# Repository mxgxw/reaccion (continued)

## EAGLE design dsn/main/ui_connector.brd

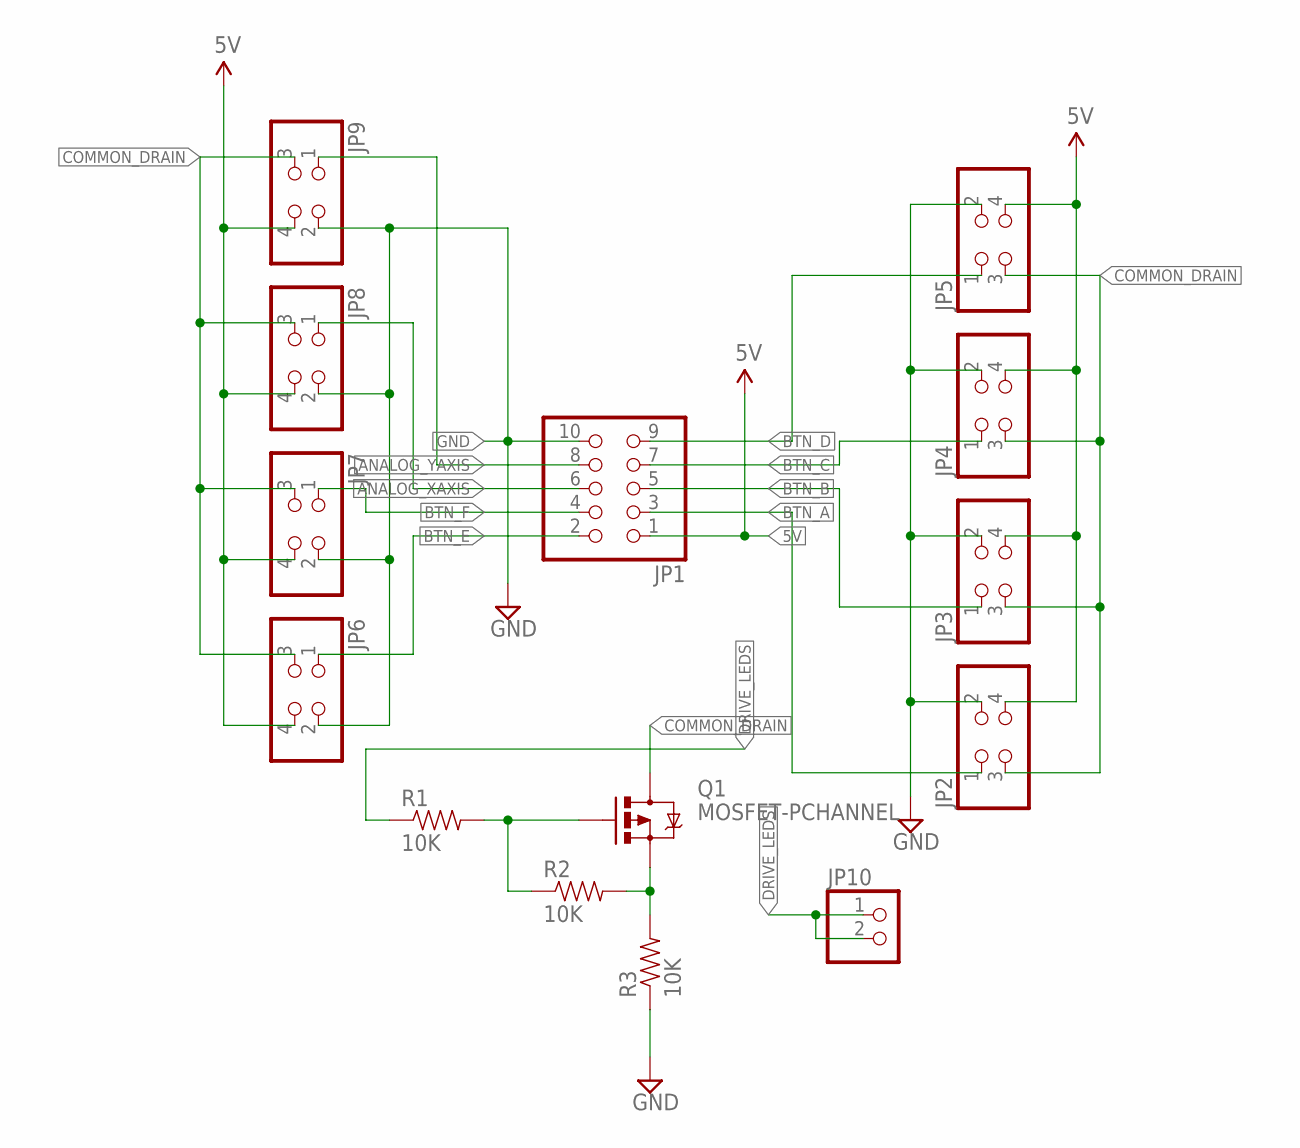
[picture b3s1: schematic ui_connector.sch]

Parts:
JP1: PINHD-2X5; 2X05
JP2, JP3, JP4, JP5, JP6, JP7, JP8, JP9: PINHD-2X2; 2X02
JP10: PINHD-1X2; 1X02
Q1: MOSFET-PCHANNEL; SOT23-3
R1, R2, R3: 10K; 0805

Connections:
5V: JP1.1, JP2.4, JP3.4, JP4.4, JP5.4, JP6.4, JP7.4, JP8.4, JP9.4
ANALOG_XAXIS: JP1.6, JP8.1
ANALOG_YAXIS: JP1.8, JP9.1
BTN_A: JP1.3, JP2.1
BTN_B: JP1.5, JP3.1
BTN_C: JP1.7, JP4.1
BTN_D: JP1.9, JP5.1
BTN_E: JP1.2, JP6.1
BTN_F: JP1.4, JP7.1
COMMON_DRAIN: JP2.3, JP3.3, JP4.3, JP5.3, JP6.3, JP7.3, JP8.3, JP9.3, Q1.3 (D)
DRIVE_LEDS: JP10.1, JP10.2, R1.1
GND: JP1.10, JP2.2, JP3.2, JP4.2, JP5.2, JP6.2, JP7.2, JP8.2, JP9.2, R3.1
unnamed: Q1.2 (S), R2.2, R3.2
unnamed: Q1.1 (G), R1.2, R2.1

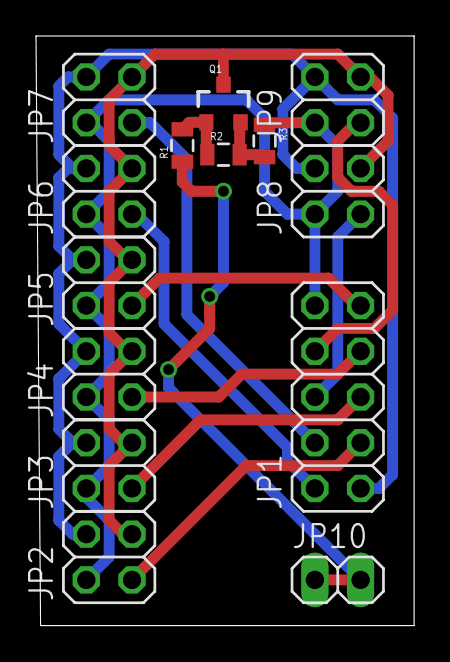
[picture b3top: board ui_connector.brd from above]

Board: 2 copper layers, 21.0 x 32.8 mm, 14 parts (0 on the bottom side), 14 nets.

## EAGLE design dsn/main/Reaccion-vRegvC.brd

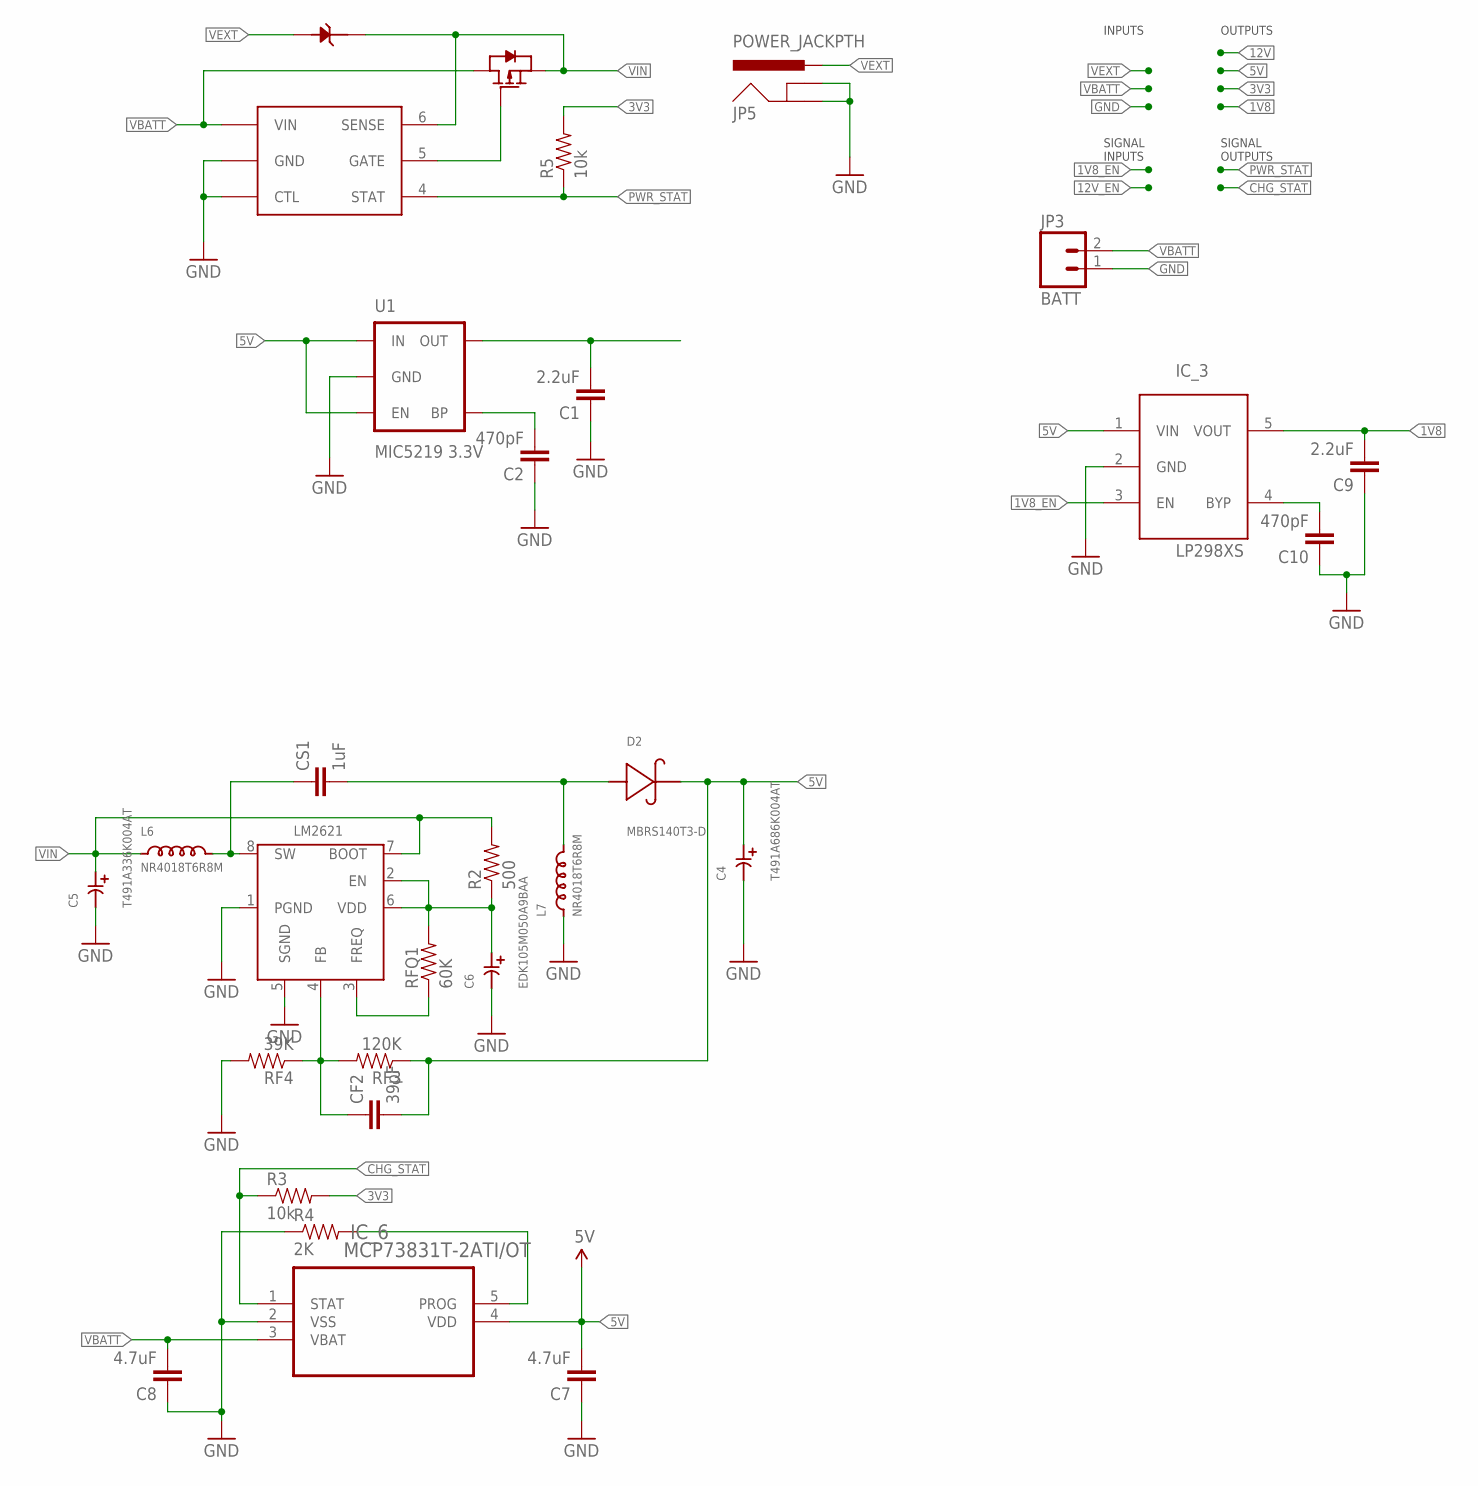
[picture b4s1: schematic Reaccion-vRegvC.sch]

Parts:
C1, C9: 2.2uF; 0805
C2, C10: 470pF; 0805
C4: T491A686K004AT; 3216-18
C5: T491A336K004AT; 3216-18
C6: EDK105M050A9BAA
C7, C8: 4.7uF; 0805
CF2: 39pF; 0805
CS1: 1uF; 0805
D2: MBRS140T3-D; MBRS140T3G
D4: 1N5819HW-7-F; SOD123
IC_1: LTC4412; SOT23-6L
IC_3: LP298XS; SOT23-5L
IC_4: LM2621; R-PDSO-G8
IC_6: MCP73831T-2ATI/OT; SOT95P300X145-5N
JP3: BATT; JST-2-PTH-NS
JP5: POWER_JACKPTH; POWER_JACK_PTH
L6, L7: NR4018T6R8M; NR4018/NRS4018
Q9: SI2301CDS; SOT23
R2: 500; 0805
R3, R5: 10k; 0805
R4: 2K; 0805
RF3: 120K; 0805
RF4: 39K; 0805
RFQ1: 60K; 0805
U1: MIC5219 3.3V; SOT23-5

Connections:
1V8: C9.2, IC_3.5 (VOUT)
1V8_EN: IC_3.3 (EN)
3V3: C1.2, R3.2, R5.2, U1.5 (OUT)
5V: C4.1, C7.2, CF2.2, D2.2, IC_3.1 (VIN), IC_6.4 (VDD), RF3.1, U1.1 (IN), U1.3 (EN)
CHG_STAT: IC_6.1 (STAT), R3.1
GND: C1.1, C2.1, C4.2, C5.2, C6.P$2, C7.1, C8.1, C9.1, C10.1, IC_1.2 (GND), IC_1.3 (CTL), IC_3.2 (GND), IC_4.1 (PGND), IC_4.5 (SGND), IC_6.2 (VSS), JP3.1, JP5.GND, JP5.GNDBREAK, L7.P$1, R4.1, RF4.2, U1.2 (GND)
unnamed: C2.2, U1.4 (BP)
unnamed: CS1.1, IC_4.8 (SW), L6.P$2
unnamed: C6.P$1, IC_4.2 (EN), IC_4.6 (VDD), R2.1, RFQ1.2
unnamed: IC_4.3 (FREQ), RFQ1.1
unnamed: CF2.1, IC_4.4 (FB), RF3.2, RF4.1
unnamed: CS1.2, D2.1, L7.P$2
unnamed: IC_6.5 (PROG), R4.2
unnamed: IC_1.5 (GATE), Q9.1 (GATE)
unnamed: C10.2, IC_3.4 (BYP)
PWR_STAT: IC_1.4 (STAT), R5.1
VBATT: C8.2, IC_1.1 (VIN), IC_6.3 (VBAT), JP3.2, Q9.3 (DRAIN)
VEXT: D4.2 (ANODE), JP5.PWR
VIN: C5.1, D4.1 (CATHODE), IC_1.6 (SENSE), IC_4.7 (BOOT), L6.P$1, Q9.2 (SOURCE), R2.2

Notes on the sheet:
INPUTS
OUTPUTS
SIGNAL INPUTS
SIGNAL OUTPUTS

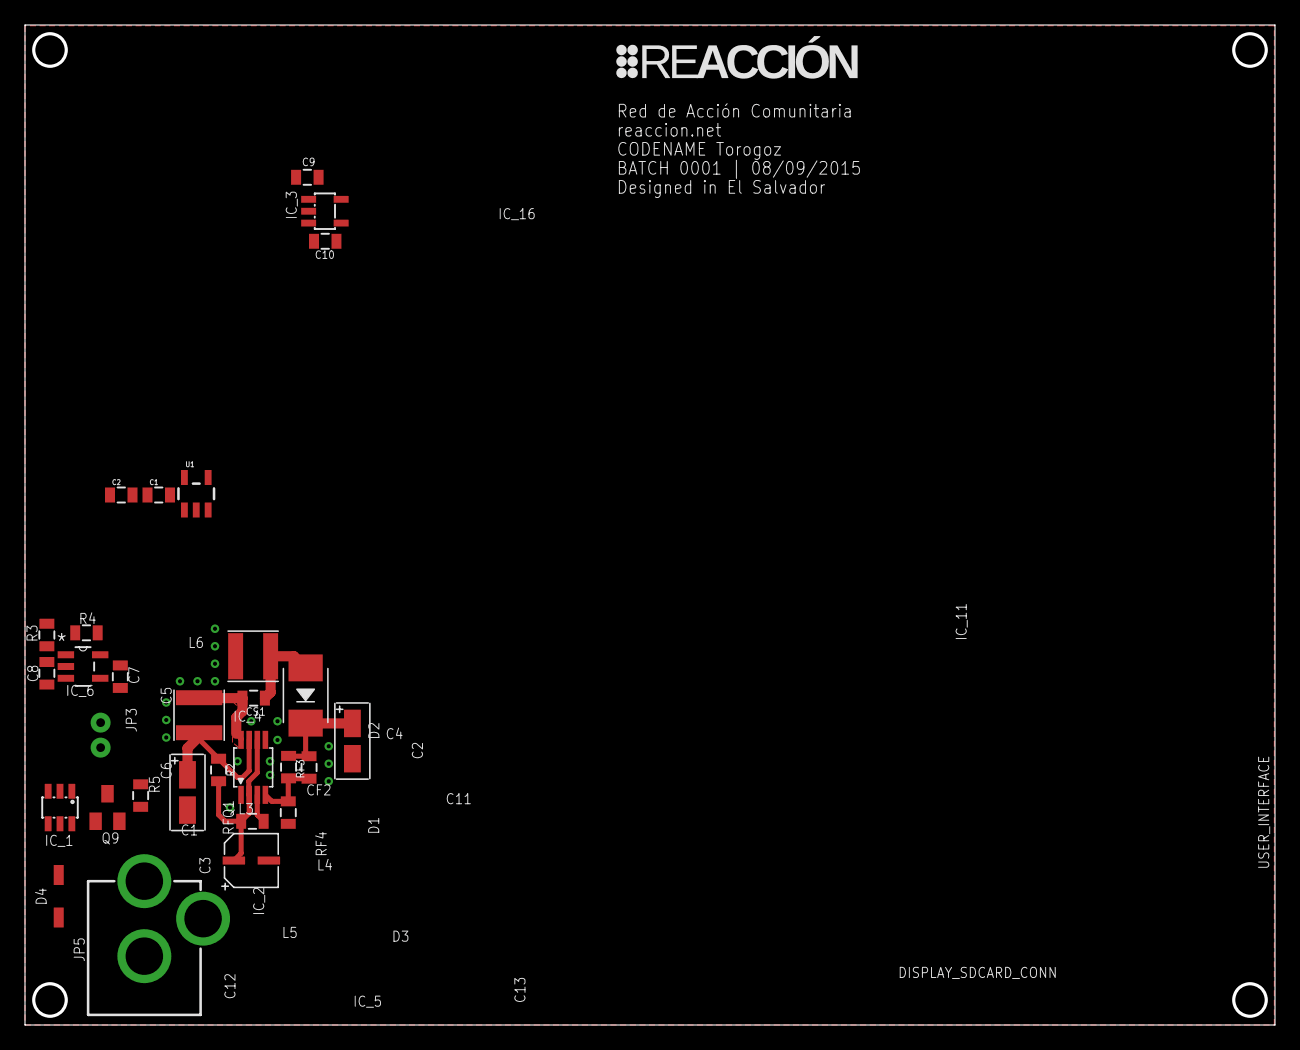
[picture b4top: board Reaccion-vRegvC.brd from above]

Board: 2 copper layers, 100.0 x 80.0 mm, 30 parts (0 on the bottom side), 18 nets.

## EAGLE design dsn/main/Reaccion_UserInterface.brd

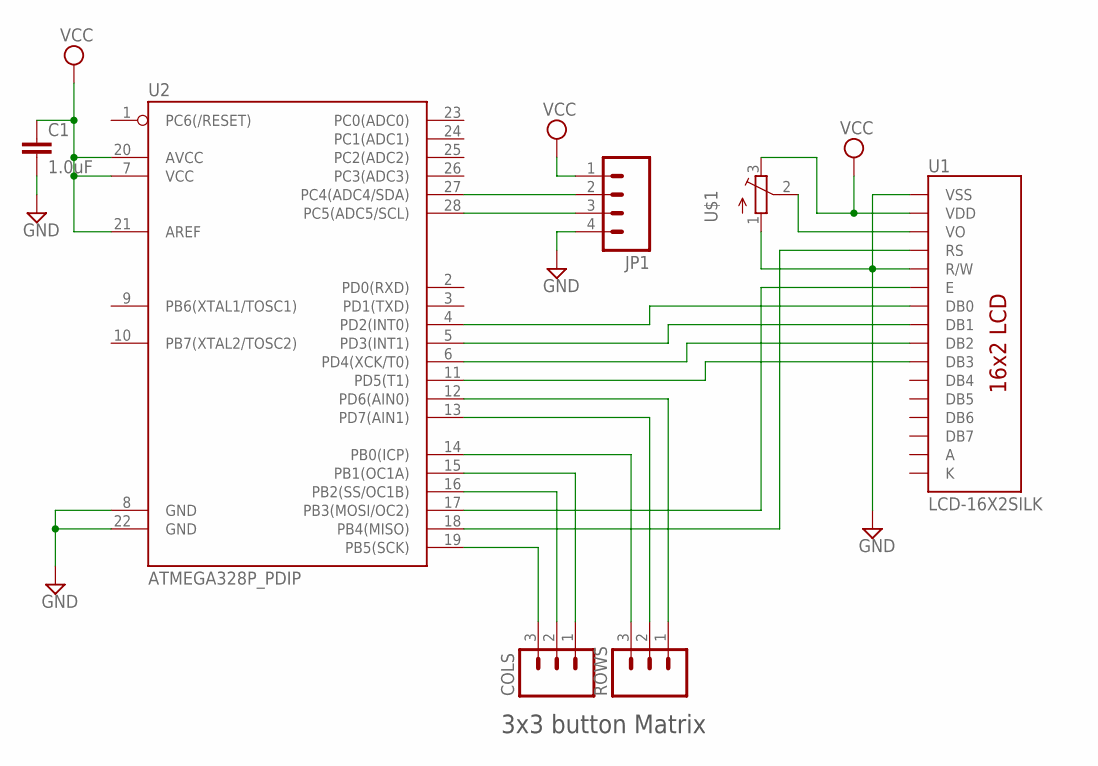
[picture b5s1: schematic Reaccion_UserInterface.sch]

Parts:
C1: 1.0uF; 0805
COLS: M03; JST-3-SMD
JP1: M04PTH; 1X04
ROWS: M03; JST-3-SMD
U1: LCD-16X2SILK; LCD-16X2
U2: ATMEGA328P_PDIP; DIL28-3
U$1: TRIMPOTTC33X; TC33X

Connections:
A: U1.15 (A)
GND: C1.2, JP1.4, U1.1 (VSS), U1.5 (R/W), U2.8 (GND), U2.22 (GND), U$1.1 (A)
K: U1.16 (K)
unnamed: JP1.2, U2.27 (PC4(ADC4/SDA))
unnamed: JP1.3, U2.28 (PC5(ADC5/SCL))
unnamed: U1.7 (DB0), U2.4 (PD2(INT0))
unnamed: U1.8 (DB1), U2.5 (PD3(INT1))
unnamed: U1.9 (DB2), U2.6 (PD4(XCK/T0))
unnamed: U1.10 (DB3), U2.11 (PD5(T1))
unnamed: U1.6 (E), U2.17 (PB3(MOSI/OC2))
unnamed: U1.4 (RS), U2.18 (PB4(MISO))
unnamed: COLS.3, U2.19 (PB5(SCK))
unnamed: U1.3 (VO), U$1.2 (S)
unnamed: COLS.2, U2.16 (PB2(SS/OC1B))
unnamed: COLS.1, U2.15 (PB1(OC1A))
unnamed: ROWS.3, U2.14 (PB0(ICP))
unnamed: ROWS.2, U2.13 (PD7(AIN1))
unnamed: ROWS.1, U2.12 (PD6(AIN0))
VCC: C1.1, JP1.1, U1.2 (VDD), U2.7 (VCC), U2.20 (AVCC), U2.21 (AREF), U$1.3 (E)

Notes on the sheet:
3x3 button Matrix

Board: 2 copper layers, 7 parts (5 on the bottom side), 17 nets, no tracks yet.

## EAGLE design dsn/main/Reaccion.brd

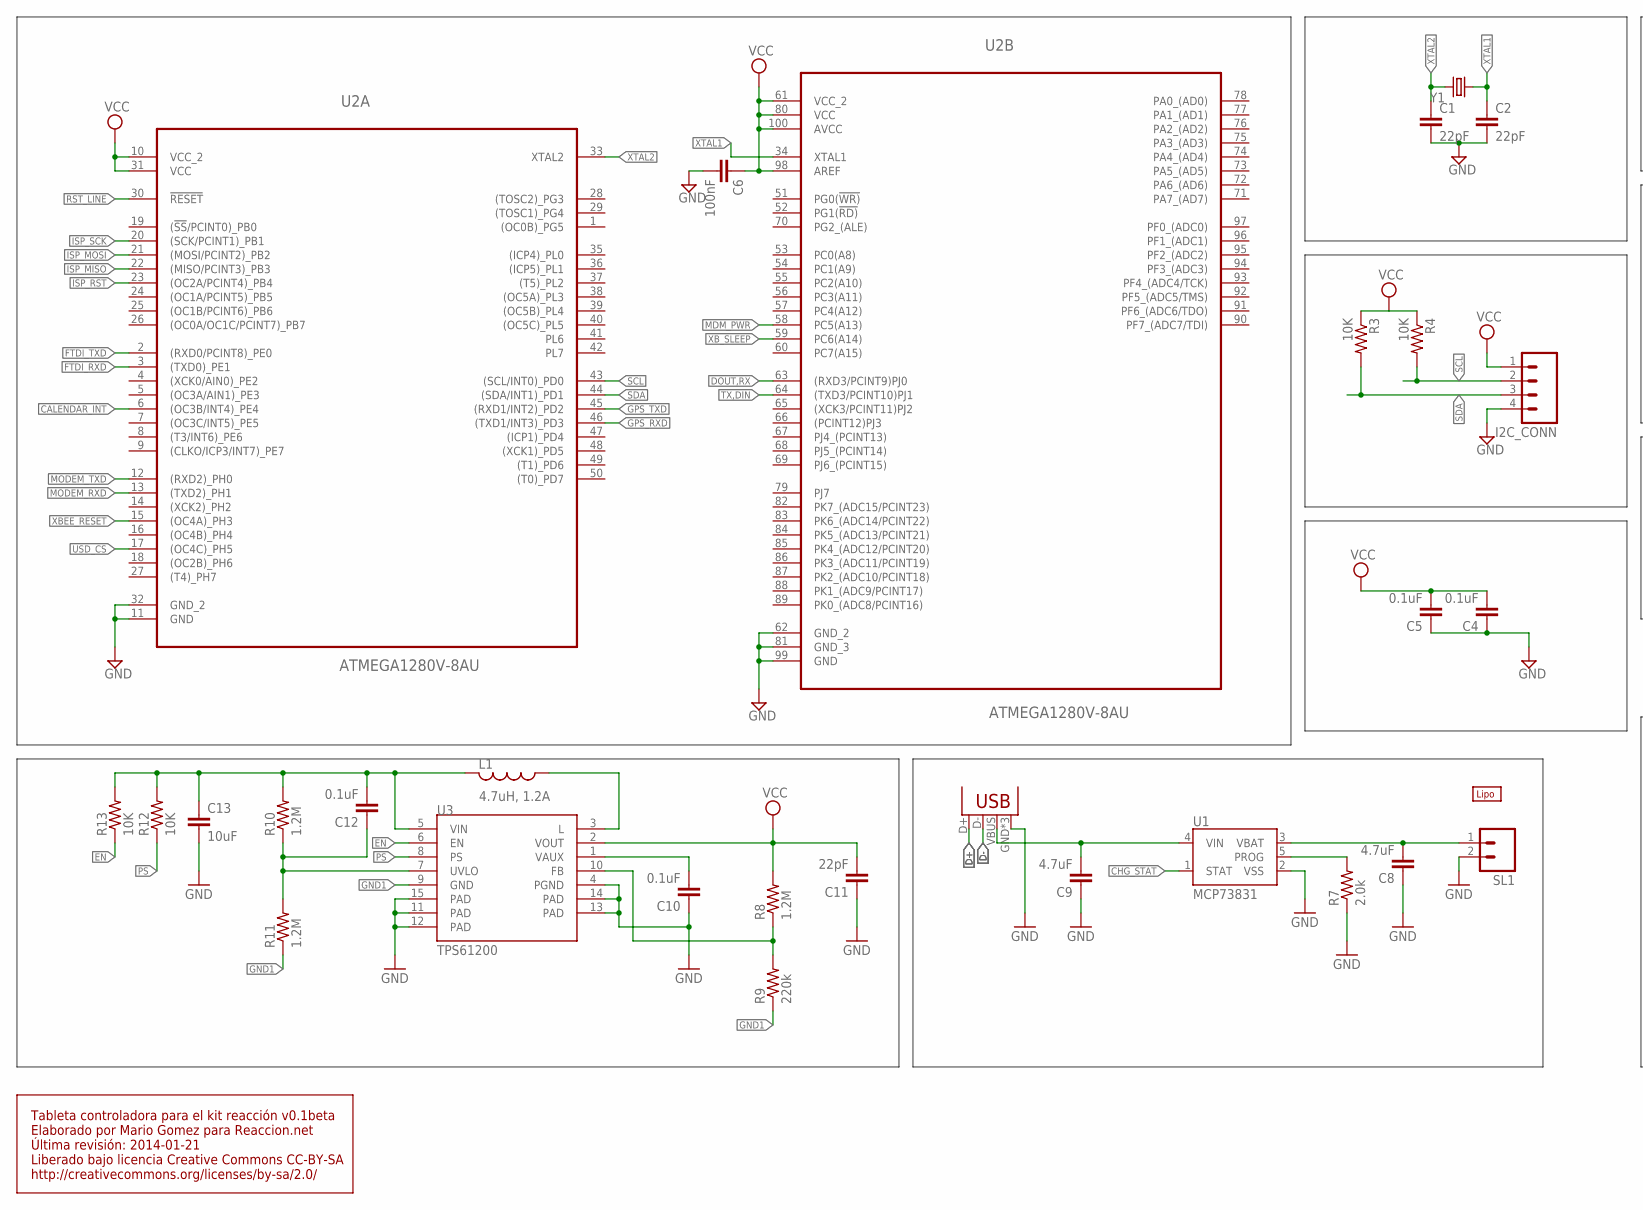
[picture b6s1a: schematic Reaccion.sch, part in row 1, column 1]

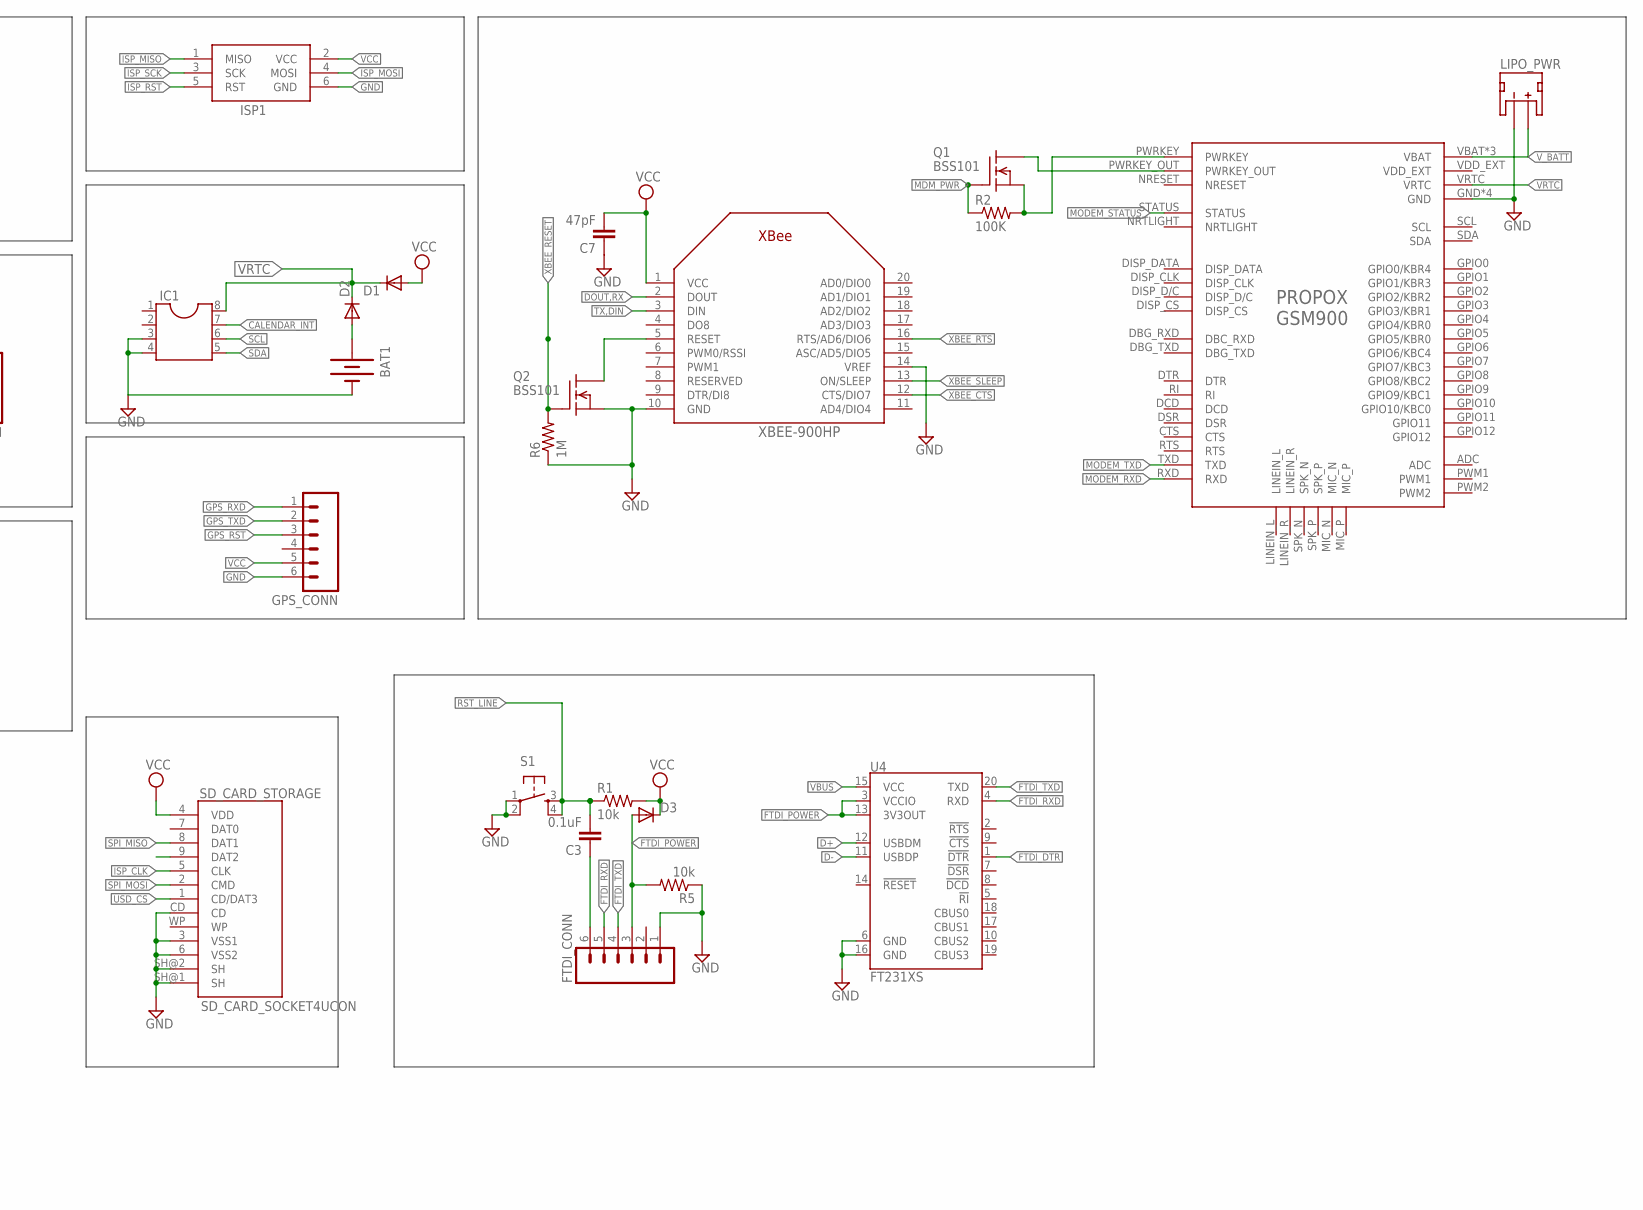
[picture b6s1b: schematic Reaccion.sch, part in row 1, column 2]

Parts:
BAT1: BATTERY12PTH; BATTCON_12MM_PTH
C1, C2, C11: 22pF; 0805
C3, C4, C5, C10, C12: 0.1uF; 0805
C6: 100nF; 0805
C7: 47pF; 0805
C8, C9: 4.7uF; 0603-CAP
C13: 10uF; 1206
D1, D2, D3: DIODESOD; SOD-323
FTDI_CONN: M06SIP; 1X06
GPS_CONN: M06SIP; 1X06
GSM_MODEM: PROPOXGSM900; CONN-13X2
I2C_CONN: M04PTH; 1X04
IC1: DIL8; DIL08
ISP1: AVRISP-6; AVRISP
JP1: USB-MICROB
L1: 4.7uH, 1.2A; CDRH2D09
LIPO_PWR: JST_2MM_MALE; JST-2-SMD
Q1, Q2: BSS101; TO92
R1, R5: 10k; 0805
R2: 100K; 0805
R3, R4: 10K; 0805
R6: 1M; 0805
R7: 2.0k; 0603-RES
R8, R10, R11: 1.2M; 0603-RES
R9: 220k; 0603-RES
R12, R13: 10K; 0603-RES
S1: TAC_SWITCHPTH; TACTILE-PTH
SD_CARD_STORAGE: SD_CARD_SOCKET4UCON; SDCARD_4UCONN
SL1: M02; 02P
U1: MCP73831; SOT23-5
U2: ATMEGA1280V-8AU; QFP50P1600X1600X120-100N
U3: TPS61200; QFN-10_PAD
U4: FT231XS; SSOP20_L
U$2: LIPO-OUTLINE2000; LIPO-2000
XBEE-900HP: XBEE
Y1: CRYSTAL10.5X4.8; CRYSTAL-SMD-10.5X4.8-2PIN

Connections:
CALENDAR_INT: IC1.7, U2.6 ((OC3B/INT4)_PE4)
CHG_STAT: U1.1 (STAT)
D+: JP1.D+, U4.12 (USBDM)
D-: JP1.D-, U4.11 (USBDP)
DOUT,RX: U2.63 ((RXD3/PCINT9)PJ0), XBEE-900HP.2 (DOUT)
EN: R13.1, U3.6 (EN)
FTDI_DTR: C3.1, FTDI_CONN.6, U4.1 (!DTR)
FTDI_POWER: D3.2 (A), FTDI_CONN.3, R5.2, U4.3 (VCCIO), U4.13 (3V3OUT)
FTDI_RXD: FTDI_CONN.5, U2.3 ((TXD0)_PE1), U4.4 (RXD)
FTDI_TXD: FTDI_CONN.4, U2.2 ((RXD0/PCINT8)_PE0), U4.20 (TXD)
GND: BAT1.GND (-), C1.2, C2.2, C4.1, C5.1, C6.2, C7.1, C8.1, C9.1, C10.1, C11.1, C13.2, FTDI_CONN.1, GPS_CONN.6, GSM_MODEM.GND, GSM_MODEM.GND2 (GND), GSM_MODEM.GND3 (GND), GSM_MODEM.GND4 (GND), I2C_CONN.4, IC1.3, IC1.4, ISP1.6 (GND), JP1.GND, JP1.MT1 (GND), JP1.MT2 (GND), LIPO_PWR.1 (-), Q2.1 (S), R5.1, R6.1, R7.1, S1.1, S1.2, SD_CARD_STORAGE.3 (VSS1), SD_CARD_STORAGE.6 (VSS2), SD_CARD_STORAGE.CD, SD_CARD_STORAGE.SH@1 (SH), SD_CARD_STORAGE.SH@2 (SH), SL1.2, U1.2 (VSS), U2.11 (GND), U2.32 (GND_2), U2.62 (GND_2), U2.81 (GND_3), U2.99 (GND), U3.4 (PGND), U3.11 (PAD), U3.12 (PAD), U3.13 (PAD), U3.14 (PAD), U3.15 (PAD), U4.6 (GND), U4.16 (GND), XBEE-900HP.10 (GND), XBEE-900HP.14 (VREF)
GND1: R9.1, R11.1, U3.9 (GND)
GPS_RST: GPS_CONN.3
GPS_RXD: GPS_CONN.1, U2.46 ((TXD1/INT3)_PD3)
GPS_TXD: GPS_CONN.2, U2.45 ((RXD1/INT2)_PD2)
ISP_CLK: SD_CARD_STORAGE.5 (CLK)
ISP_MISO: ISP1.1 (MISO), U2.22 ((MISO/PCINT3)_PB3)
ISP_MOSI: ISP1.4 (MOSI), U2.21 ((MOSI/PCINT2)_PB2)
ISP_RST: ISP1.5 (RST), U2.23 ((OC2A/PCINT4)_PB4)
ISP_SCK: ISP1.3 (SCK), U2.20 ((SCK/PCINT1)_PB1)
MDM_PWR: Q1.2 (G), R2.1, U2.58 (PC5(A13))
MODEM_RXD: GSM_MODEM.RXD, U2.13 ((TXD2)_PH1)
MODEM_STATUS: GSM_MODEM.STATUS
MODEM_TXD: GSM_MODEM.TXD, U2.12 ((RXD2)_PH0)
unnamed: BAT1.VCC@1 (+), D2.2 (A)
unnamed: R7.2, U1.5 (PROG)
unnamed: Q2.3 (D), XBEE-900HP.5 (RESET)
unnamed: GSM_MODEM.PWRKEY_OUT, Q1.3 (D)
unnamed: GSM_MODEM.PWRKEY, Q1.1 (S), R2.2
unnamed: C10.2, U3.1 (VAUX)
unnamed: R8.1, R9.2, U3.10 (FB)
unnamed: L1.P$1 (1), U3.3 (L)
unnamed: C12.1, R10.1, R11.2, U3.7 (UVLO)
PS: R12.1, U3.8 (PS)
RST_LINE: C3.2, R1.1, S1.3, S1.4, U2.30 (!RESET)
SCL: I2C_CONN.2, IC1.6, R4.2, U2.43 ((SCL/INT0)_PD0)
SDA: I2C_CONN.3, IC1.5, R3.2, U2.44 ((SDA/INT1)_PD1)
SPI_MISO: SD_CARD_STORAGE.8 (DAT1)
SPI_MOSI: SD_CARD_STORAGE.2 (CMD)
TX,DIN: U2.64 ((TXD3/PCINT10)PJ1), XBEE-900HP.3 (DIN)
USD_CS: SD_CARD_STORAGE.1 (CD/DAT3), U2.17 ((OC4C)_PH5)
VBUS: C9.2, JP1.VBUS, U1.4 (VIN), U4.15 (VCC)
VCC: C4.2, C5.2, C6.1, C7.2, C11.2, D1.2 (A), D3.1 (C), GPS_CONN.5, I2C_CONN.1, ISP1.2 (VCC), R1.2, R3.1, R4.1, R8.2, SD_CARD_STORAGE.4 (VDD), U2.10 (VCC_2), U2.31 (VCC), U2.61 (VCC_2), U2.80 (VCC), U2.98 (AREF), U2.100 (AVCC), U3.2 (VOUT), XBEE-900HP.1 (VCC)
VRTC: D1.1 (C), D2.1 (C), GSM_MODEM.VRTC, IC1.8
V_BATT: C8.2, C12.2, C13.1, GSM_MODEM.VBAT, GSM_MODEM.VBAT2 (VBAT), GSM_MODEM.VBAT3 (VBAT), L1.P$2 (2), LIPO_PWR.2 (+), R10.2, R12.2, R13.2, SL1.1, U1.3 (VBAT), U3.5 (VIN)
XBEE_CTS: XBEE-900HP.12 (CTS/DIO7)
XBEE_RESET: Q2.2 (G), R6.2, U2.15 ((OC4A)_PH3)
XBEE_RTS: XBEE-900HP.16 (RTS/AD6/DIO6)
XBEE_SLEEP: XBEE-900HP.13 (ON/SLEEP)
XB_SLEEP: U2.59 (PC6(A14))
XTAL1: C2.1, U2.34 (XTAL1), Y1.P$1 (1)
XTAL2: C1.1, U2.33 (XTAL2), Y1.P$2 (2)

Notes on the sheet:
Tableta controladora para el kit reacción v0.1beta Elaborado por Mario Gomez para Reaccion.net Última revisión: 2014-01-21 Liberado bajo licencia Creative Commons CC-BY-SA http://creativecommons.org/licenses/by-sa/2.0/

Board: 2 copper layers, 51 parts (0 on the bottom side), 42 nets, no tracks yet.

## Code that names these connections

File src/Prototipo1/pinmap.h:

/* BEGIN SIM900 PIN SETUP */
#define SIM900_PWR        2
#define SIM900_RESET      23
#define SIM900_RI         30
#define SIM900_STATUS     31
/* BEGIN GPS PIN SETUP */
#define GPS_ONOFF         14
#define GPS_TM            15
#define GPS_WU            16
#define GPS_RST           17
/* BEGIN XBEE PIN SETUP */
#define XBEE_RESET        28
#define XBEE_SLEEP        22
/* BEGIN BLUETOOTH PIN SETUP */
#define BT_EN             27
#define BT_CMD            33
/* BEGIN SCREEN & SD CARD READER PIN SETUP */
#define DISPLAY_DC        4
#define DISPLAY_SDCS      5
#define SPI1_CS           6
#define SPI1_MISO         11
#define SPI1_MOSI         12
#define SPI1_SCK          13
#define DISPLAY_BL        20
#define SPI1_RST          3
/* BEGIN OTHER IO PIN SETUP */
#define EN_12V            26
#define BUZZER_ACT        23
#define CHG_STAT          1
#define PWR_STAT          0
/* EXTERNAL INTERRUPTS */
#define IO_INT0           32
#define BTN_A             9
#define BTN_B             8
#define BTN_C             6
#define BTN_D             7
#define BTN_E             10
#define BTN_F             11

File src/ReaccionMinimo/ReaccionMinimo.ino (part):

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#define BTN_3 A2
#define BTN_4 A3
// RF IO
#define RF_RX 11
#define RF_TX 12
#define RF_PTT 0
// Buzzer
#define BUZZER 7
// Battery level
#define BATT_LVL A7
// User interface
#define HEARTBEAT 5
/************************ END IO MAPPING **************************/
/************************ BEGIN GLOBALS ***************************/
PROGRAM_STATE state = BOOT;
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
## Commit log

2015-11-03 local init for testing
2015-11-09 PCB re-design
2015-11-09 Laen's DRC corrections, small modifications
2015-11-17 Added power source corrections
2015-11-17 Updated gitignore
2015-11-17 Endlines normalized
2015-12-26 Initial release for Prototipo1
2016-08-21 Added latest changes
2016-09-07 Reaccion-Minimo.sch for edu purposes finished.
2016-09-11 Reaccion Minimo UI finished. RX send tested.
2016-09-13 Tested implementation. Heartbeat changed to RGB.
2016-11-08 Added Reaccion-Minimo PASTO
2017-01-28 Added support for PASTO Minimo version
